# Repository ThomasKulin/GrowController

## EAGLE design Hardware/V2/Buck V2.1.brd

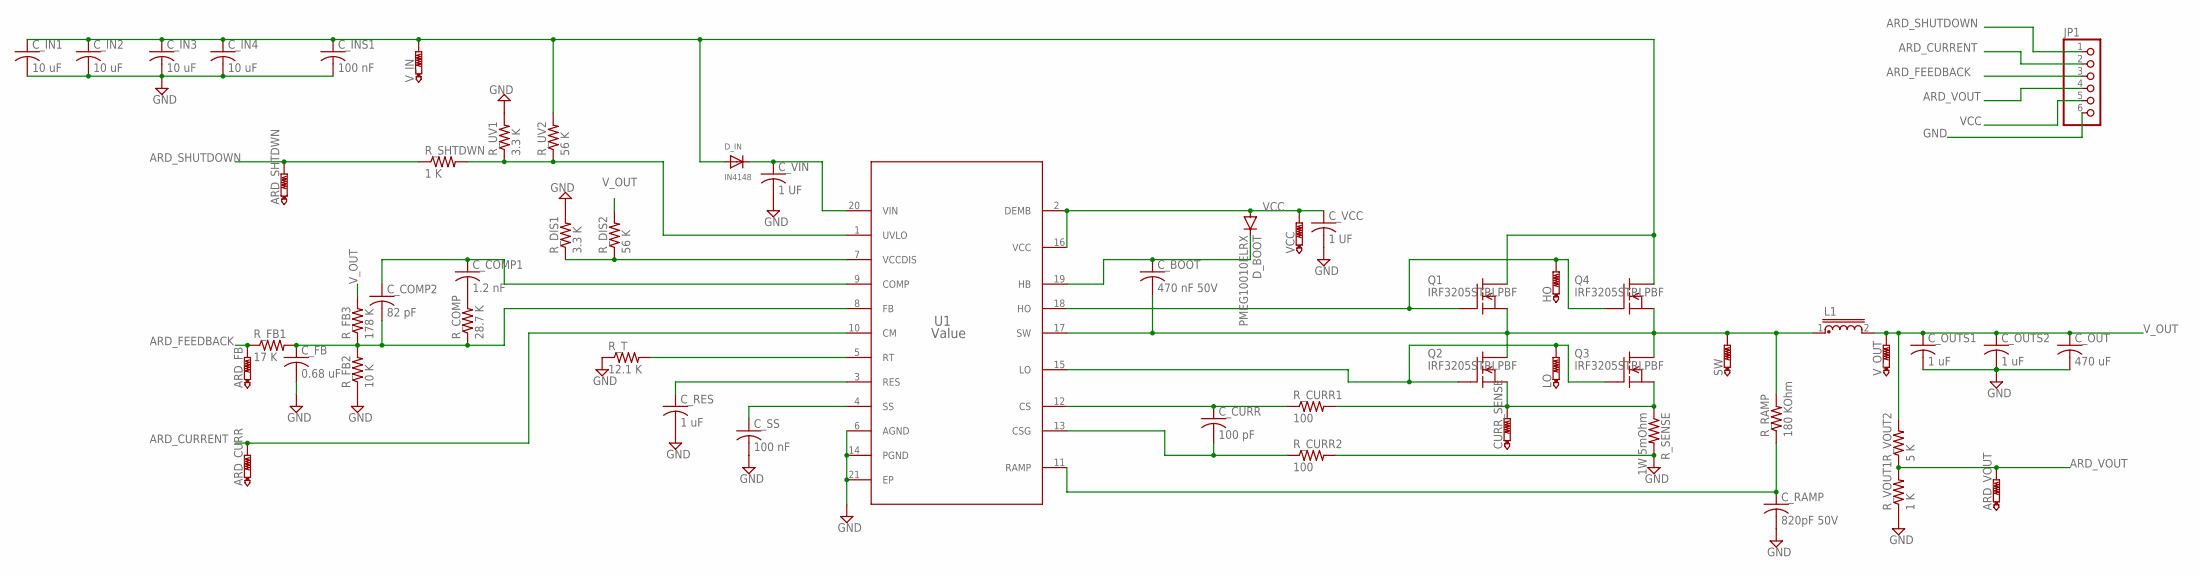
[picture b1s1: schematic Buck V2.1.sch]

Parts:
ARD_CURR: PTR1TP20R; TP20R
ARD_FB: PTR1TP20R; TP20R
ARD_SHTDWN: PTR1TP20R; TP20R
ARD_VOUT: PTR1TP20R; TP20R
CURR_SENSE: PTR1TP20R; TP20R
C_BOOT: 470 nF 50V; C0603
C_COMP1: 1.2 nF; C0603
C_COMP2: 82 pF; C0603
C_CURR: 100 pF; C0603
C_FB: 0.68 uF; C0603
C_IN1, C_IN2, C_IN3, C_IN4: 10 uF; C1206
C_INS1: 100 nF; C0603
C_OUT: 470 uF; CAP_PANASONIC_H13
C_OUTS1, C_OUTS2: 1 uF; C0805
C_RAMP: 820pF 50V; C0603
C_RES: 1 uF; C0603
C_SS: 100 nF; C0603
C_VCC: 1 UF; C0603
C_VIN: 1 UF; C0603
D_BOOT: PMEG10010ELRX; SOD123
D_IN: IN4148; SOD-123
HO: PTR1TP20R; TP20R
JP1: PINHD-1X6; 1X06
L1: 17.5X17.5_INDUCTOR_SMD
LO: PTR1TP20R; TP20R
Q1, Q2, Q3, Q4: IRF3205STRLPBF; D2PAK
R_COMP: 28.7 K; R0603
R_CURR1, R_CURR2: 100; R0603
R_DIS1: 3.3 K; R0603
R_DIS2: 56 K; R0603
R_FB1: 17 K; R0603
R_FB2: 10 K; R0603
R_FB3: 178 K; R0603
R_RAMP: 180 KOhm; R0603
R_SENSE: 1W 5mOhm; R2512
R_SHTDWN: 1 K; R0603
R_T: 12.1 K; R0603
R_UV1: 3.3 K; R0603
R_UV2: 56 K; R0603
R_VOUT1: 1 K; R0603
R_VOUT2: 5 K; R0603
SW: PTR1TP20R; TP20R
U1: Value; PWP0020A
VCC: PTR1TP20R; TP20R
V_IN: PTR1TP20R; TP20R
V_OUT: PTR1TP20R; TP20R

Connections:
ARD_CURRENT: ARD_CURR.TP, JP1.2, U1.10 (CM)
ARD_FEEDBACK: ARD_FB.TP, JP1.3, R_FB1.1
ARD_SHUTDOWN: ARD_SHTDWN.TP, JP1.1, R_SHTDWN.1
ARD_VOUT: ARD_VOUT.TP, JP1.4, R_VOUT1.2, R_VOUT2.1
GND: C_FB.2, C_IN1.2, C_IN2.2, C_IN3.2, C_IN4.2, C_INS1.2, C_OUT.P$1 (1), C_OUTS1.2, C_OUTS2.2, C_RAMP.2, C_RES.2, C_SS.2, C_VCC.2, C_VIN.2, JP1.6, R_CURR2.2, R_DIS1.2, R_FB2.1, R_SENSE.2, R_T.1, R_UV1.2, R_VOUT1.1, U1.6 (AGND), U1.14 (PGND), U1.21 (EP)
unnamed: C_BOOT.1, D_BOOT.C, U1.19 (HB)
unnamed: C_BOOT.2, L1.1, Q1.3 (S), Q2.2 (D), Q3.2 (D), Q4.3 (S), R_RAMP.2, SW.TP, U1.17 (SW)
unnamed: CURR_SENSE.TP, Q2.3 (S), Q3.3 (S), R_CURR1.2, R_SENSE.1
unnamed: C_RAMP.1, R_RAMP.1, U1.11 (RAMP)
unnamed: LO.TP, Q2.1 (G), Q3.1 (G), U1.15 (LO)
unnamed: HO.TP, Q1.1 (G), Q4.1 (G), U1.18 (HO)
unnamed: C_COMP1.2, R_COMP.2
unnamed: C_VIN.1, D_IN.C, U1.20 (VIN)
unnamed: R_SHTDWN.2, R_UV1.1, R_UV2.1, U1.1 (UVLO)
unnamed: R_DIS1.1, R_DIS2.1, U1.7 (VCCDIS)
unnamed: C_COMP1.1, C_COMP2.1, U1.9 (COMP)
unnamed: C_COMP2.2, C_FB.1, R_COMP.1, R_FB1.2, R_FB2.2, R_FB3.1, U1.8 (FB)
unnamed: R_T.2, U1.5 (RT)
unnamed: C_RES.1, U1.3 (RES)
unnamed: C_SS.1, U1.4 (SS)
unnamed: C_CURR.1, R_CURR1.1, U1.12 (CS)
unnamed: C_CURR.2, R_CURR2.1, U1.13 (CSG)
unnamed: C_IN1.1, C_IN2.1, C_IN3.1, C_IN4.1, C_INS1.1, D_IN.A, Q1.2 (D), Q4.2 (D), R_UV2.2, V_IN.TP
VCC: C_VCC.1, D_BOOT.A, JP1.5, U1.2 (DEMB), U1.16 (VCC), VCC.TP
V_OUT: C_OUT.P$2 (2), C_OUTS1.1, C_OUTS2.1, L1.2, R_DIS2.2, R_FB3.2, R_VOUT2.2, V_OUT.TP

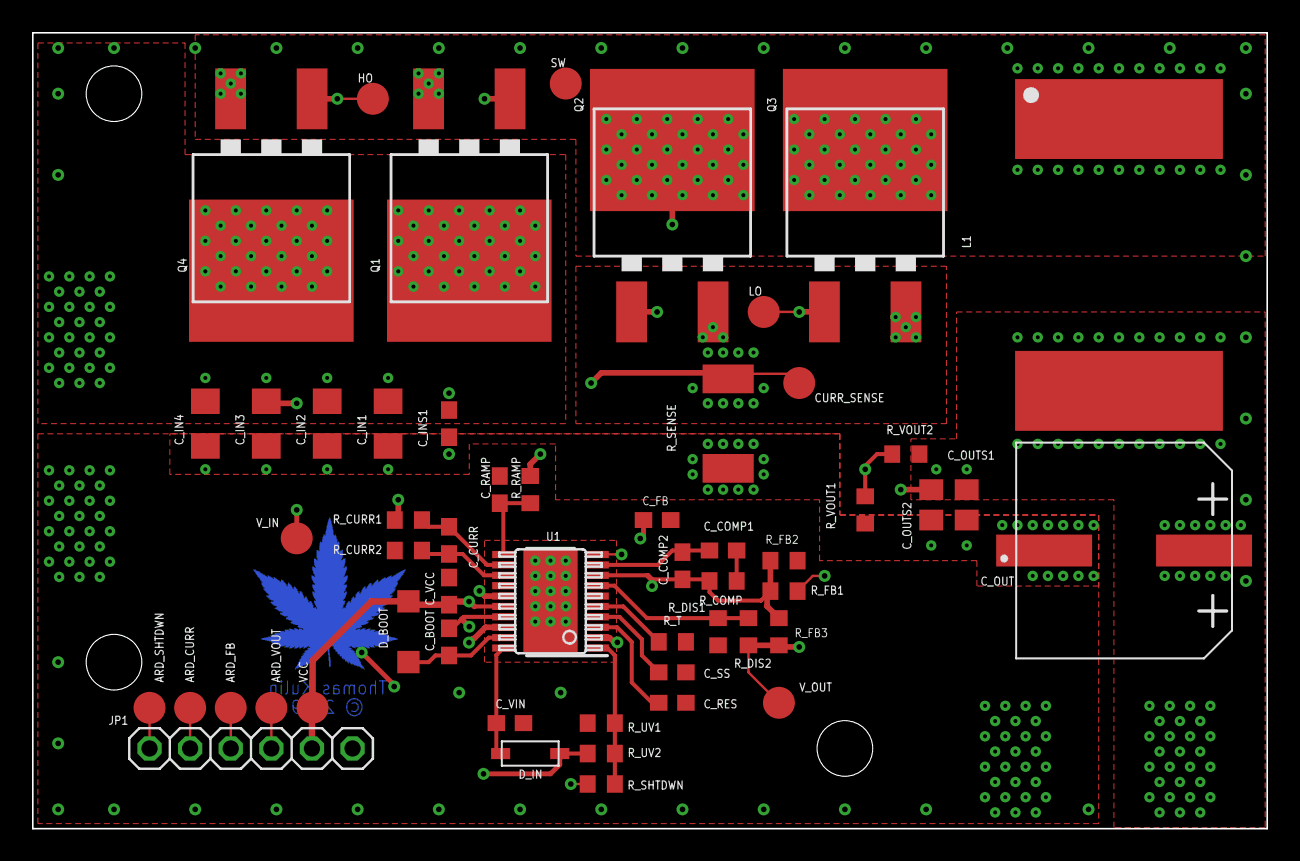
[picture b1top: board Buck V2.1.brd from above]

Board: 4 copper layers, 77.2 x 49.8 mm, 54 parts (0 on the bottom side), 25 nets.

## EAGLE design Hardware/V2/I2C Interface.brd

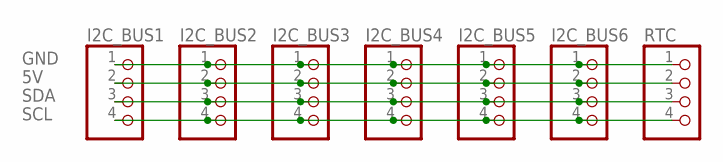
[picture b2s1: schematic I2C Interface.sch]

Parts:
I2C_BUS1, I2C_BUS2, I2C_BUS3, I2C_BUS4, I2C_BUS5, I2C_BUS6: PINHD-1X4; 1X04
RTC: PINHD-1X4; 1X04

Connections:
5V: I2C_BUS1.2, I2C_BUS2.2, I2C_BUS3.2, I2C_BUS4.2, I2C_BUS5.2, I2C_BUS6.2, RTC.2
GND: I2C_BUS1.1, I2C_BUS2.1, I2C_BUS3.1, I2C_BUS4.1, I2C_BUS5.1, I2C_BUS6.1, RTC.1
SCL: I2C_BUS1.4, I2C_BUS2.4, I2C_BUS3.4, I2C_BUS4.4, I2C_BUS5.4, I2C_BUS6.4, RTC.4
SDA: I2C_BUS1.3, I2C_BUS2.3, I2C_BUS3.3, I2C_BUS4.3, I2C_BUS5.3, I2C_BUS6.3, RTC.3

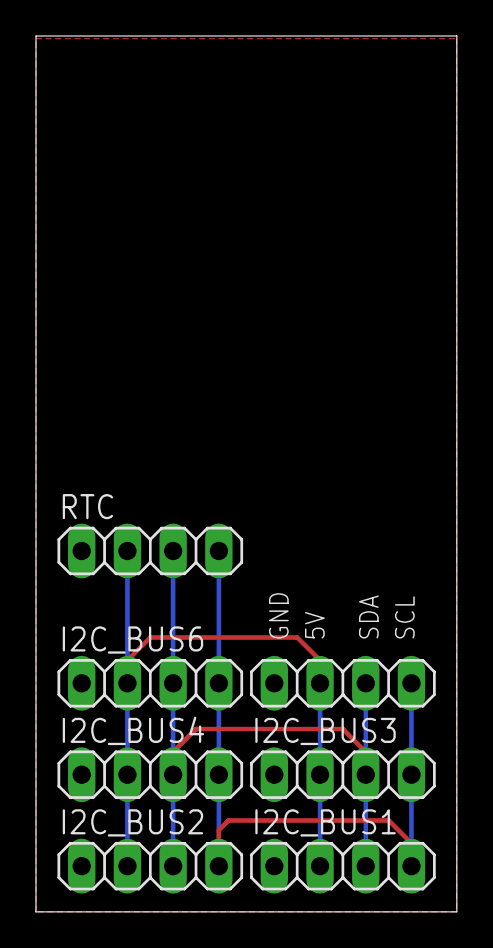
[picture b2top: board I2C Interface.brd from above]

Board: 4 copper layers, 23.4 x 48.7 mm, 7 parts (0 on the bottom side), 4 nets.

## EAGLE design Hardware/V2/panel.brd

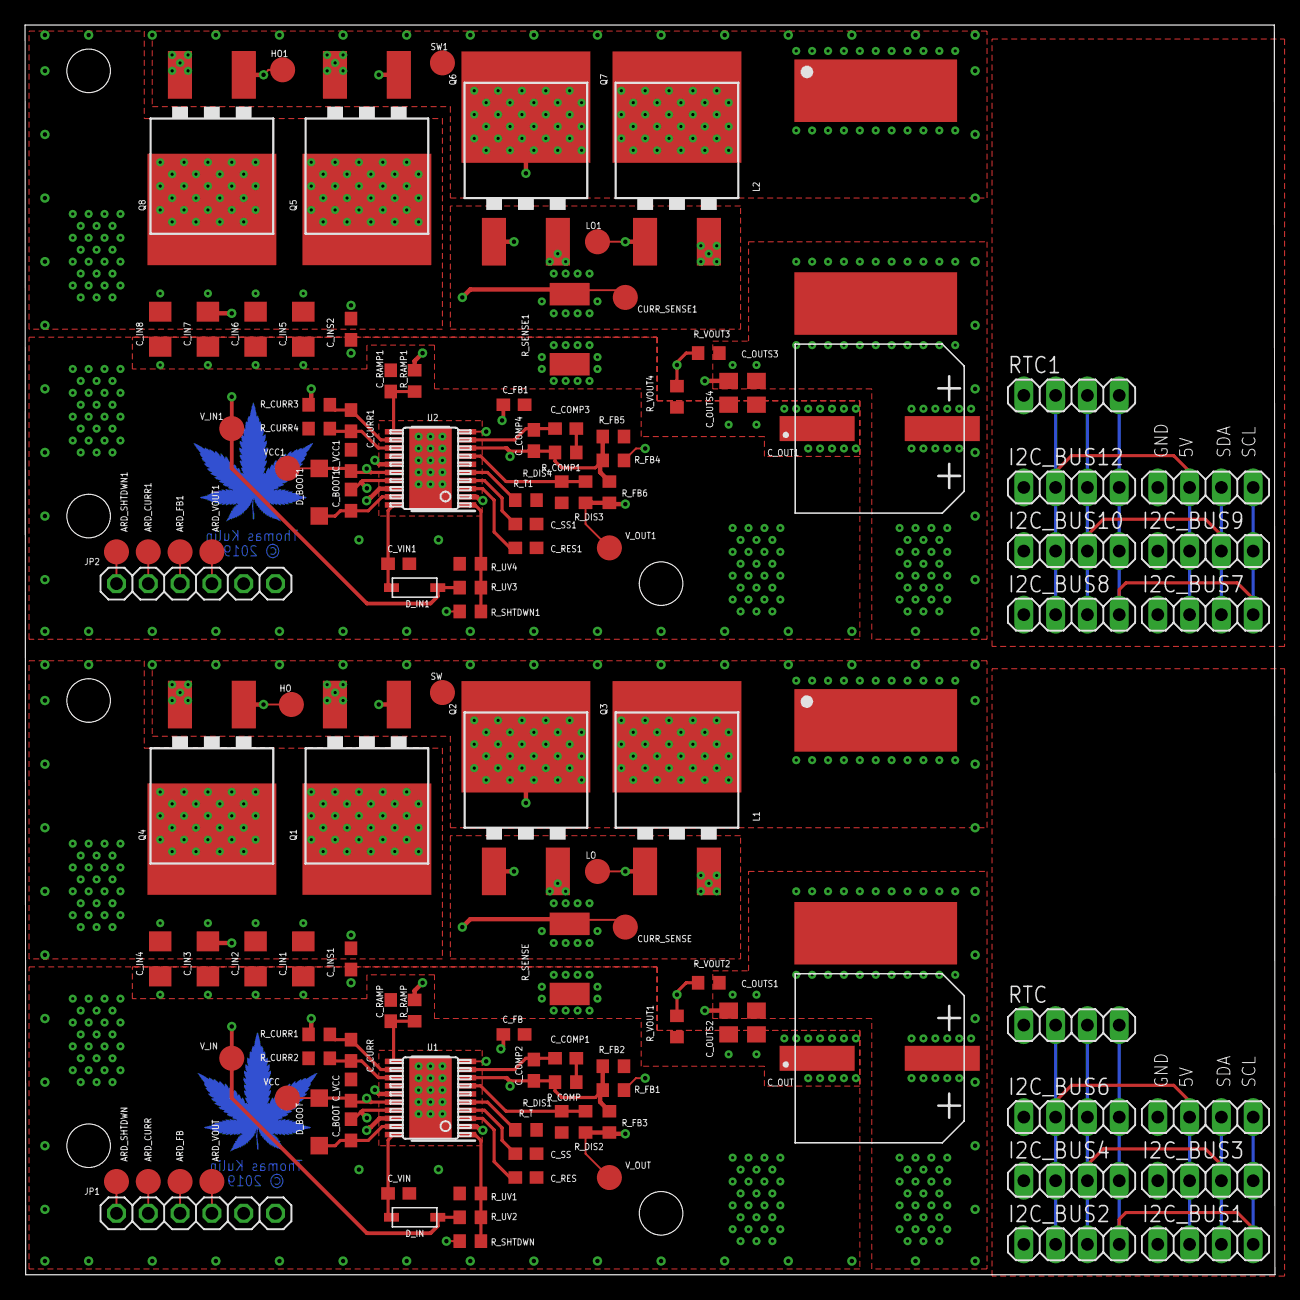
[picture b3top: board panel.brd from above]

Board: 4 copper layers, 99.8 x 99.8 mm, 122 parts (0 on the bottom side), 58 nets.

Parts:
ARD_CURR, ARD_CURR1: PTR1TP20R; TP20R
ARD_FB, ARD_FB1: PTR1TP20R; TP20R
ARD_SHTDWN, ARD_SHTDWN1: PTR1TP20R; TP20R
ARD_VOUT, ARD_VOUT1: PTR1TP20R; TP20R
CURR_SENSE, CURR_SENSE1: PTR1TP20R; TP20R
C_BOOT, C_BOOT1: 470 nF 50V; C0603
C_COMP1, C_COMP3: 1.2 nF; C0603
C_COMP2, C_COMP4: 82 pF; C0603
C_CURR, C_CURR1: 100 pF; C0603
C_FB, C_FB1: 0.68 uF; C0603
C_IN1, C_IN2, C_IN3, C_IN4, C_IN5, C_IN6, C_IN7, C_IN8: 10 uF; C1206
C_INS1, C_INS2: 100 nF; C0603
C_OUT, C_OUT1: 470 uF; CAP_PANASONIC_H13
C_OUTS1, C_OUTS2, C_OUTS3, C_OUTS4: 1 uF; C0805
C_RAMP, C_RAMP1: 820pF 50V; C0603
C_RES, C_RES1: 1 uF; C0603
C_SS, C_SS1: 100 nF; C0603
C_VCC, C_VCC1: 1 UF; C0603
C_VIN, C_VIN1: 1 UF; C0603
D_BOOT, D_BOOT1: PMEG10010ELRX; SOD123
D_IN, D_IN1: IN4148; SOD-123
HO, HO1: PTR1TP20R; TP20R
I2C_BUS1, I2C_BUS2, I2C_BUS3, I2C_BUS4, I2C_BUS5, I2C_BUS6, I2C_BUS7, I2C_BUS8, I2C_BUS9, I2C_BUS10, I2C_BUS11, I2C_BUS12: 1X04
JP1, JP2: 1X06
L1, L2: 17.5X17.5_INDUCTOR_SMD
LO, LO1: PTR1TP20R; TP20R
Q1, Q2, Q3, Q4, Q5, Q6, Q7, Q8: IRF3205STRLPBF; D2PAK
RTC, RTC1: 1X04
R_COMP, R_COMP1: 28.7 K; R0603
R_CURR1, R_CURR2, R_CURR3, R_CURR4: 100; R0603
R_DIS1, R_DIS4: 3.3 K; R0603
R_DIS2, R_DIS3: 56 K; R0603
R_FB1, R_FB4: 17 K; R0603
R_FB2, R_FB5: 10 K; R0603
R_FB3, R_FB6: 178 K; R0603
R_RAMP, R_RAMP1: 180 KOhm; R0603
R_SENSE, R_SENSE1: 1W 5mOhm; R2512
R_SHTDWN, R_SHTDWN1: 1 K; R0603
R_T, R_T1: 12.1 K; R0603
R_UV1, R_UV4: 3.3 K; R0603
R_UV2, R_UV3: 56 K; R0603
R_VOUT1, R_VOUT4: 1 K; R0603
R_VOUT2, R_VOUT3: 5 K; R0603
SW, SW1: PTR1TP20R; TP20R
U1, U2: Value; PWP0020A
VCC, VCC1: PTR1TP20R; TP20R
V_IN, V_IN1: PTR1TP20R; TP20R
V_OUT, V_OUT1: PTR1TP20R; TP20R

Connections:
5V: I2C_BUS1.2, I2C_BUS2.2, I2C_BUS3.2, I2C_BUS4.2, I2C_BUS5.2, I2C_BUS6.2, RTC.2
5V1: I2C_BUS7.2, I2C_BUS8.2, I2C_BUS9.2, I2C_BUS10.2, I2C_BUS11.2, I2C_BUS12.2, RTC1.2
ARD_CURRENT: ARD_CURR.TP, JP1.2, U1.10
ARD_CURRENT1: ARD_CURR1.TP, JP2.2, U2.10
ARD_FEEDBACK: ARD_FB.TP, JP1.3, R_FB1.1
ARD_FEEDBACK1: ARD_FB1.TP, JP2.3, R_FB4.1
ARD_SHUTDOWN: ARD_SHTDWN.TP, JP1.1, R_SHTDWN.1
ARD_SHUTDOWN1: ARD_SHTDWN1.TP, JP2.1, R_SHTDWN1.1
ARD_VOUT: ARD_VOUT.TP, JP1.4, R_VOUT1.2, R_VOUT2.1
ARD_VOUT1: ARD_VOUT1.TP, JP2.4, R_VOUT3.1, R_VOUT4.2
GND: C_FB.2, C_IN1.2, C_IN2.2, C_IN3.2, C_IN4.2, C_INS1.2, C_OUT.P$1, C_OUTS1.2, C_OUTS2.2, C_RAMP.2, C_RES.2, C_SS.2, C_VCC.2, C_VIN.2, JP1.5, JP1.6, R_CURR2.2, R_DIS1.2, R_FB2.1, R_SENSE.2, R_T.1, R_UV1.2, R_VOUT1.1, U1.6, U1.14, U1.21
GND1: C_FB1.2, C_IN5.2, C_IN6.2, C_IN7.2, C_IN8.2, C_INS2.2, C_OUT1.P$1, C_OUTS3.2, C_OUTS4.2, C_RAMP1.2, C_RES1.2, C_SS1.2, C_VCC1.2, C_VIN1.2, JP2.5, JP2.6, R_CURR4.2, R_DIS4.2, R_FB5.1, R_SENSE1.2, R_T1.1, R_UV4.2, R_VOUT4.1, U2.6, U2.14, U2.21
GND2: I2C_BUS1.1, I2C_BUS2.1, I2C_BUS3.1, I2C_BUS4.1, I2C_BUS5.1, I2C_BUS6.1, RTC.1
GND3: I2C_BUS7.1, I2C_BUS8.1, I2C_BUS9.1, I2C_BUS10.1, I2C_BUS11.1, I2C_BUS12.1, RTC1.1
unnamed: C_VCC.1, D_BOOT.A, U1.2, U1.16, VCC.TP
unnamed: C_BOOT.1, D_BOOT.C, U1.19
unnamed: C_BOOT.2, L1.1, Q1.3, Q2.2, Q3.2, Q4.3, R_RAMP.2, SW.TP, U1.17
unnamed: CURR_SENSE.TP, Q2.3, Q3.3, R_CURR1.2, R_SENSE.1
unnamed: C_RAMP.1, R_RAMP.1, U1.11
unnamed: C_VCC1.1, D_BOOT1.A, U2.2, U2.16, VCC1.TP
unnamed: LO.TP, Q2.1, Q3.1, U1.15
unnamed: HO.TP, Q1.1, Q4.1, U1.18
unnamed: C_COMP1.2, R_COMP.2
unnamed: C_VIN.1, D_IN.C, U1.20
unnamed: R_SHTDWN.2, R_UV1.1, R_UV2.1, U1.1
unnamed: C_BOOT1.1, D_BOOT1.C, U2.19
unnamed: R_DIS1.1, R_DIS2.1, U1.7
unnamed: C_COMP1.1, C_COMP2.1, U1.9
unnamed: C_COMP2.2, C_FB.1, R_COMP.1, R_FB1.2, R_FB2.2, R_FB3.1, U1.8
unnamed: R_T.2, U1.5
unnamed: C_RES.1, U1.3
unnamed: C_SS.1, U1.4
unnamed: C_CURR.1, R_CURR1.1, U1.12
unnamed: C_CURR.2, R_CURR2.1, U1.13
unnamed: C_IN1.1, C_IN2.1, C_IN3.1, C_IN4.1, C_INS1.1, D_IN.A, Q1.2, Q4.2, R_UV2.2, V_IN.TP
unnamed: C_BOOT1.2, L2.1, Q5.3, Q6.2, Q7.2, Q8.3, R_RAMP1.2, SW1.TP, U2.17
unnamed: CURR_SENSE1.TP, Q6.3, Q7.3, R_CURR3.2, R_SENSE1.1
unnamed: C_RAMP1.1, R_RAMP1.1, U2.11
unnamed: LO1.TP, Q6.1, Q7.1, U2.15
unnamed: HO1.TP, Q5.1, Q8.1, U2.18
unnamed: R_SHTDWN1.2, R_UV3.1, R_UV4.1, U2.1
unnamed: R_DIS3.1, R_DIS4.1, U2.7
unnamed: C_COMP3.2, R_COMP1.2
unnamed: C_COMP3.1, C_COMP4.1, U2.9
unnamed: C_COMP4.2, C_FB1.1, R_COMP1.1, R_FB4.2, R_FB5.2, R_FB6.1, U2.8
unnamed: R_T1.2, U2.5
unnamed: C_SS1.1, U2.4
unnamed: C_RES1.1, U2.3
unnamed: C_CURR1.1, R_CURR3.1, U2.12
unnamed: C_CURR1.2, R_CURR4.1, U2.13
unnamed: C_VIN1.1, D_IN1.C, U2.20
unnamed: C_IN5.1, C_IN6.1, C_IN7.1, C_IN8.1, C_INS2.1, D_IN1.A, Q5.2, Q8.2, R_UV3.2, V_IN1.TP
SCL: I2C_BUS1.4, I2C_BUS2.4, I2C_BUS3.4, I2C_BUS4.4, I2C_BUS5.4, I2C_BUS6.4, RTC.4
SCL1: I2C_BUS7.4, I2C_BUS8.4, I2C_BUS9.4, I2C_BUS10.4, I2C_BUS11.4, I2C_BUS12.4, RTC1.4
SDA: I2C_BUS1.3, I2C_BUS2.3, I2C_BUS3.3, I2C_BUS4.3, I2C_BUS5.3, I2C_BUS6.3, RTC.3
SDA1: I2C_BUS7.3, I2C_BUS8.3, I2C_BUS9.3, I2C_BUS10.3, I2C_BUS11.3, I2C_BUS12.3, RTC1.3
V_OUT: C_OUT.P$2, C_OUTS1.1, C_OUTS2.1, L1.2, R_DIS2.2, R_FB3.2, R_VOUT2.2, V_OUT.TP
V_OUT1: C_OUT1.P$2, C_OUTS3.1, C_OUTS4.1, L2.2, R_DIS3.2, R_FB6.2, R_VOUT3.2, V_OUT1.TP

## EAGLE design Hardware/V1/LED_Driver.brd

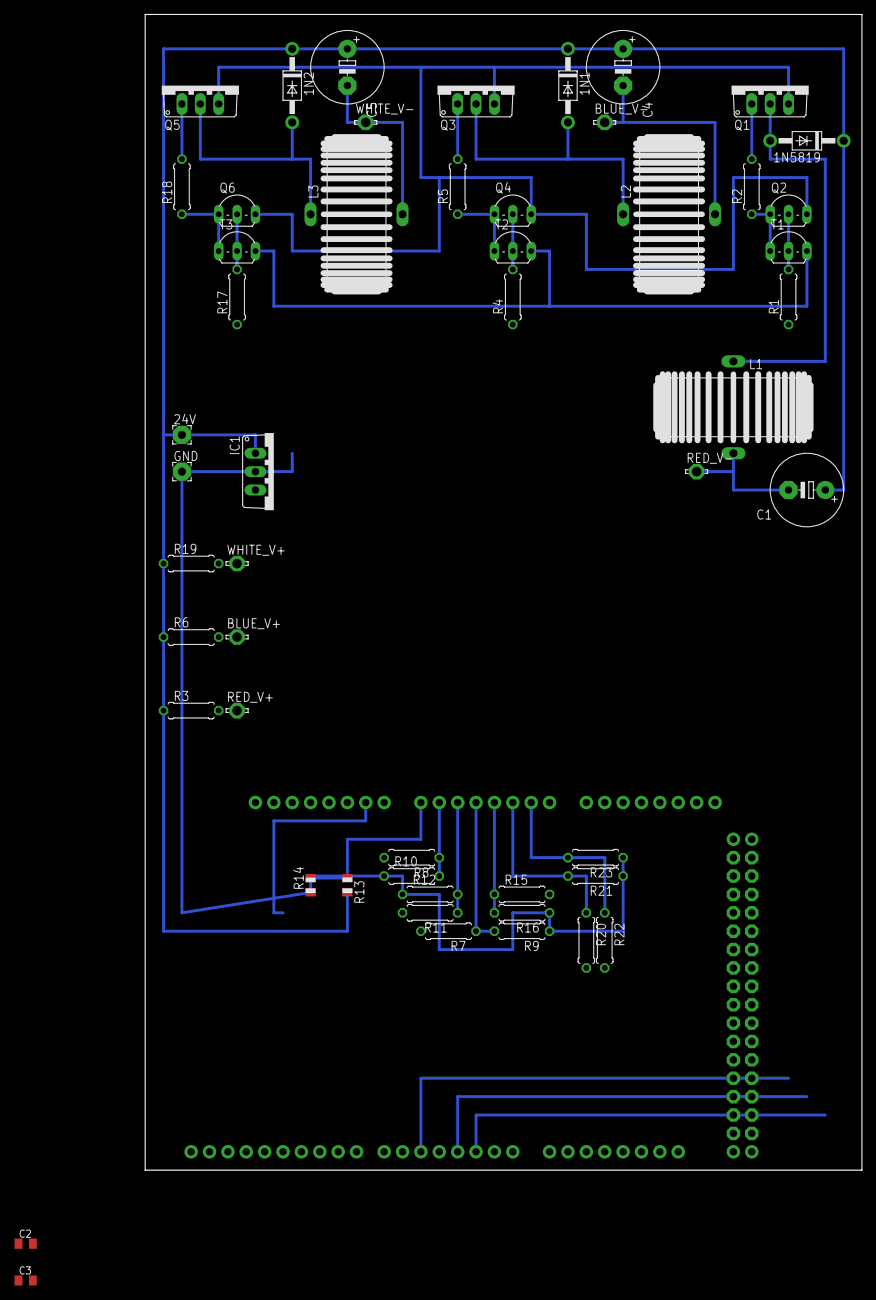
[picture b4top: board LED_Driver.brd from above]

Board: 2 copper layers, 99.0 x 159.7 mm, 53 parts (1 on the bottom side), 31 nets.

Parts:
1N1, 1N2, 1N5819: DO41-10
24V: 2,54/1,1
B2: ARDUINO_MEGA_R3FULL; ARDUINO_MEGA_NO_SILK
BLUE_V+: LSP13
BLUE_V-: LSP13
C1, C4, C5: E5-10,5
C2: 0.33uF; C0805K
C3: 0.1uF; C0805K
GND: 2,54/1,1
IC1: 7812TV; TO220V
L1, L2, L3: 10 - 100uH; SFT1030
Q1, Q3, Q5: TO220V
Q2, Q4, Q6: 2N2907; TO92-EBC-OVAL
R1, R4, R17: 1k; 0207/7
R2, R5, R18: 10; 0207/7
R3, R6, R19: 0.5; 0207/7
R7, R8, R11, R15, R20, R22: 470K; 0207/7
R9, R10, R12, R16, R21, R23: 100K; 0207/7
R13: 470K; R0805
R14: 100K; R0805
RED_V+: LSP13
RED_V-: LSP13
T1, T2, T3: 2N2222; TO92-EBC-OVAL
WHITE_V+: LSP13
WHITE_V-: LSP13

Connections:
+12V: C3.1, IC1.3, T1.C, T2.C, T3.C
+24V: 1N1.C, 1N2.C, 1N5819.C, 24V.1, C1.+, C2.1, C4.+, C5.+, IC1.1, R3.1, R6.1, R13.2, R19.1
BLUE_NEG: BLUE_V-.MP, C4.-, L2.2, R15.2
BLUE_POS: BLUE_V+.MP, R6.2, R7.2
BLUE_V+: B2.A3, R7.1, R9.2
BLUE_V-: B2.A4, R15.1, R16.2
GND: C2.2, C3.2, GND.1, IC1.2, Q1.3, Q2.C, Q3.3, Q4.C, Q5.3, Q6.C, R9.1, R10.1, R12.1, R14.1, R16.1, R21.1, R23.1
unnamed: Q2.E, R2.1, T1.E
unnamed: 1N5819.A, L1.1, Q1.2
unnamed: Q4.E, R5.1, T2.E
unnamed: Q2.B, R1.2, T1.B
unnamed: Q1.1, R2.2
unnamed: 1N1.A, L2.1, Q3.2
unnamed: Q4.B, R4.2, T2.B
unnamed: Q3.1, R5.2
unnamed: Q6.E, R18.1, T3.E
unnamed: 1N2.A, L3.1, Q5.2
unnamed: Q6.B, R17.2, T3.B
unnamed: Q5.1, R18.2
PWM_BLUE: B2.3, R4.1
PWM_RED: B2.2, R1.1
PWM_WHITE: B2.5, R17.1
RED_NEG: C1.-, L1.2, R11.2, RED_V-.MP
RED_POS: R3.2, R8.2, RED_V+.MP
RED_V+: B2.A1, R8.1, R10.2
RED_V-: B2.A2, R11.1, R12.2
V_IN: B2.A0, R13.1, R14.2
WHITE_NEG: C5.-, L3.2, R22.2, WHITE_V-.MP
WHITE_POS: R19.2, R20.2, WHITE_V+.MP
WHITE_V+: B2.A5, R20.1, R21.2
WHITE_V-: B2.A6, R22.1, R23.2

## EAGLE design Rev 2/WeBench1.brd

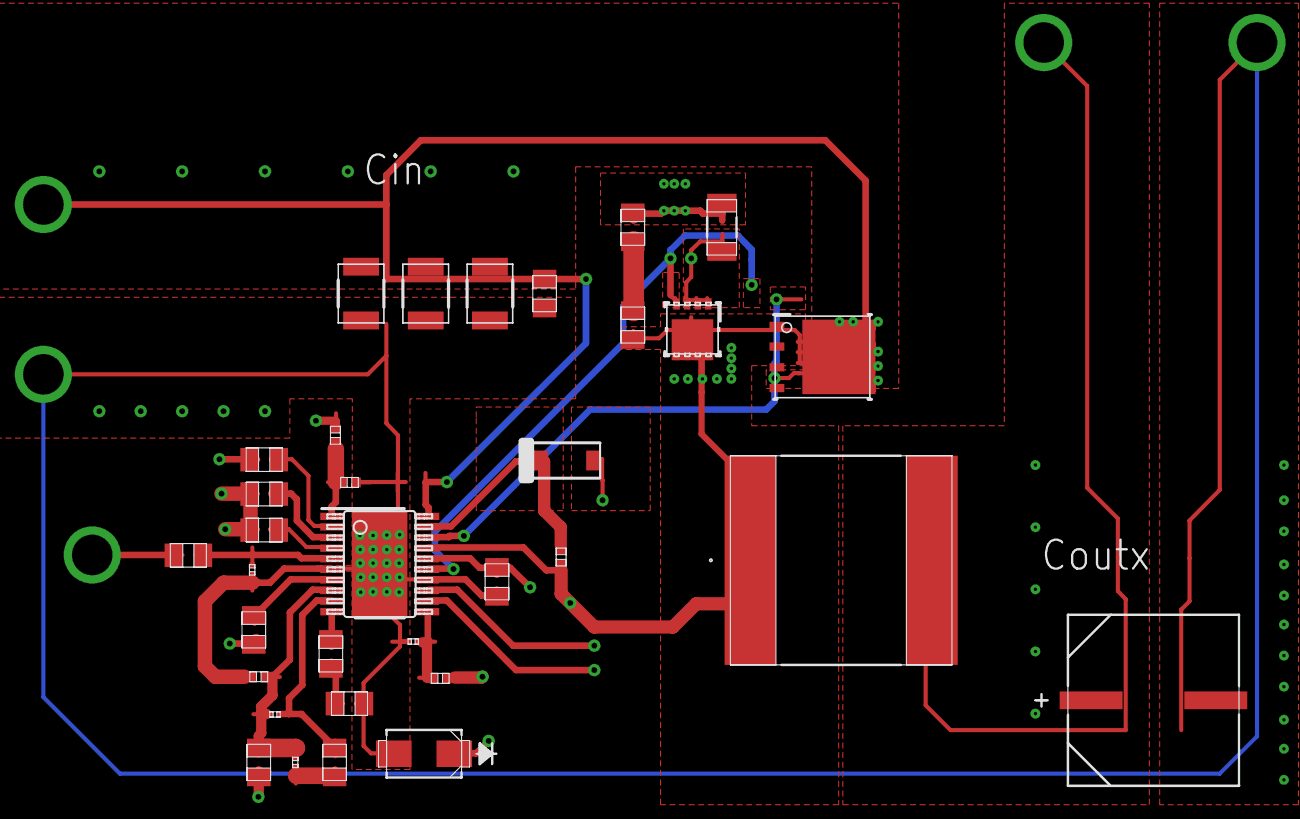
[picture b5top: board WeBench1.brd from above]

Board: 4 copper layers, 38 parts (0 on the bottom side), 22 nets.

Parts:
Cboot: 0402
Ccm: 0805
Ccomp1: 0805
Ccomp2: 0201
Cin_1, Cin_2, Cin_3: 1210_280
Cinx: 0805
Cout: CAPSMT_62_F12
Cramp: 0201
Cres: 0805
Csnub: 0805
Css: 0805
Csync: 0805
Cvcc: 0805
D1: SOD-123
D2: SMA
GND, GND1: TP-1502
L1: XAL1580
M1: DQJ0008A
M2: DNH0008A
RDemb: 0805
Rcm: 0805
Rcomp: 0201
Rfb1: 0402
Rfb2: 0805
Rramp: 0402
Rsense: 1206
Rsnub: 0805
Rt: 0201
Ruv1, Ruv2: 0402
Rvccdis: 0805
U1: PWP0020A
VIN: TP-1502
VOUT: TP-1502
VSync: TP-1502

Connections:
0: Ccm.2, Cin_1.2, Cin_2.2, Cin_3.2, Cinx.2, Cout.2, Cramp.2, Cres.2, Css.2, Cvcc.2, D2.2, GND.1, GND1.1, Rfb1.2, Rsense.2, Rsnub.1, Rt.2, Ruv1.2, U1.6, U1.13, U1.14, U1.21
1: Cvcc.1, D1.2, D2.1, RDemb.1, RDemb.2, Rvccdis.1, U1.2, U1.16
2: Ccomp2.2, Rcomp.2, Rfb1.1, Rfb2.2, U1.8
3: Cboot.2, Csnub.2, L1.1, M1.1, M1.2, M1.3, M2.5, M2.6, M2.7, M2.8, M2.9, Rramp.1, U1.17
4: Cboot.1, D1.1, U1.19
5: Cin_1.1, Cin_2.1, Cin_3.1, Cinx.1, M1.5, M1.6, M1.7, M1.8, M1.9, Ruv2.1, U1.20, VIN.1
6: Cramp.1, Rramp.2, U1.11
7: M2.1, M2.2, M2.3, Rsense.1, U1.12
8: Cout.1, L1.2, Rfb2.1, VOUT.1
9: Csync.2, Rt.1, U1.5
10: Ruv1.1, Ruv2.2, U1.1
11: Ccomp1.1, Ccomp2.1, U1.9
12: Cres.1, U1.3
13: Css.1, U1.4
15: Ccomp1.2, Rcomp.1
16: M2.4, U1.15
17: Csync.1, VSync.1
18: Csnub.1, Rsnub.2
20: Rvccdis.2, U1.7
27: Rcm.2, U1.10
35: Ccm.1, Rcm.1
S$22netdata: M1.4, U1.18

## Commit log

2019-06-28 Include rev 1 for reference. FIRST COMMIT!
2019-06-28 added revision 2 progress
2019-06-30 added schematic for Current Driver V2!
2019-07-04 Added Board Layout for Buck V1 Module
2019-07-04 Added test points, arranged silkscreen text
2019-07-15 Finished evreything, boards ordered from JLC! Hi Thomas
2019-11-05 changed file structure
2019-11-06 updated buck v2.1 to reflect actual boards ordered from JLC
2019-11-06 began work on V2 code
2019-11-08 working LED driver class with completed handling functions including filtering and working on implementing PID control. PID needs more tuning as well as current control mode
2019-11-13 stuff with Alec

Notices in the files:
Hardware/V2/Buck V2.1.brd:
© 2019
parts and their libraries:
Sparkfun-Boards: Licensing: Creative Commons ShareAlike 4.0 International - https://creativecommons.org/licenses/by-sa/4.0
